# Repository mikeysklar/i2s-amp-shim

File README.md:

# i2s-amp-shim

A direct-connect shim PCB that mates the Adafruit I2S 3W Class D amp breakout (MAX98357A, **#3006**) to a Feather. No breadboard or jumper wires needed.

## About

A passive shim with no components: two right-angle SMD sockets and five traces. The Feather plugs into one edge. The amp plugs into the other edge, standing vertical with its parts facing away from the Feather. Both sockets overhang the board (75% on the Feather side, 61% on the amp side), which keeps the shim to 17.5 × 24.9 mm.

Single copper layer, made for a home build: the outline is milled and the copper is ablated with a fiber laser, then coated in solder mask with the pads opened. Design files are in [`kicad/`](kicad/). The board comes entirely from `kicad/build_pcb.py`.

## Pinout

| Feather | Amp (#3006) | Notes |
|---------|-------------|-------|
| 3V      | Vin         | |
| GND     | GND         | |
| A0      | BCLK        | |
| A1      | LRC         | must be the pin after BCLK for RP2xxx PIO I2S |
| A2      | DIN         | |
| —       | SD          | open: amp outputs (L+R)/2 mono |
| —       | GAIN        | open: 9 dB |

### CircuitPython usage

```python
import audiobusio, board
i2s = audiobusio.I2SOut(bit_clock=board.A0, word_select=board.A1, data=board.A2)
```

## Board notes

- **No crossings.** A0→BCLK and A1→LRC are straight across. A2→DIN runs under the south end of the amp socket and comes into pin 5 from behind.
- **Traces:** 1.0 mm, the full width of the socket pads, with at least 0.6 mm between traces.
- **GND** is a routed trace. The rest of the board is unconnected copper fill with a 0.5 mm gap around every trace and pad, so the laser has less to remove. The fill stays 0.5 mm back from the outline.
- **Front silk:** a label sits past each end of each socket's pin row, where the soldered socket doesn't cover it: 3V and A2 on the Feather side, VIN and LRC on the amp side.
- **Back silk** (burned with the laser): the board name, an A0/A1/A2 → BCLK/LRC/DIN table, and the date.
- **3D view:** the sockets use flat-SMT models made by `kicad/make_3d.py` (FreeCAD) from KiCad's right-angle socket. A Feather RP2350 and the #3006 amp are shown plugged in, using Adafruit's models from [Adafruit_CAD_Parts](https://github.com/adafruit/Adafruit_CAD_Parts). They're board-only, render-only footprints (VIS1, VIS2) with no copper, kept out of the schematic and BOM, and written by `kicad/gen_render_fps.py`.
- **Etch art:** `kicad/etch/etch-FCu-MIRRORED-1to1.pdf` (print at 100%) and `etch-FCu-reference.pdf`.

## Photos

### Laser-ablated copper

### Solder mask with the pads opened

### Assembled, next to its paste stencil

## Layout

## License

[MIT](LICENSE)

The KiCad-derived 3D models in `kicad/3dmodels/` are CC-BY-SA 4.0. The Adafruit board models are MIT, from Adafruit_CAD_Parts.

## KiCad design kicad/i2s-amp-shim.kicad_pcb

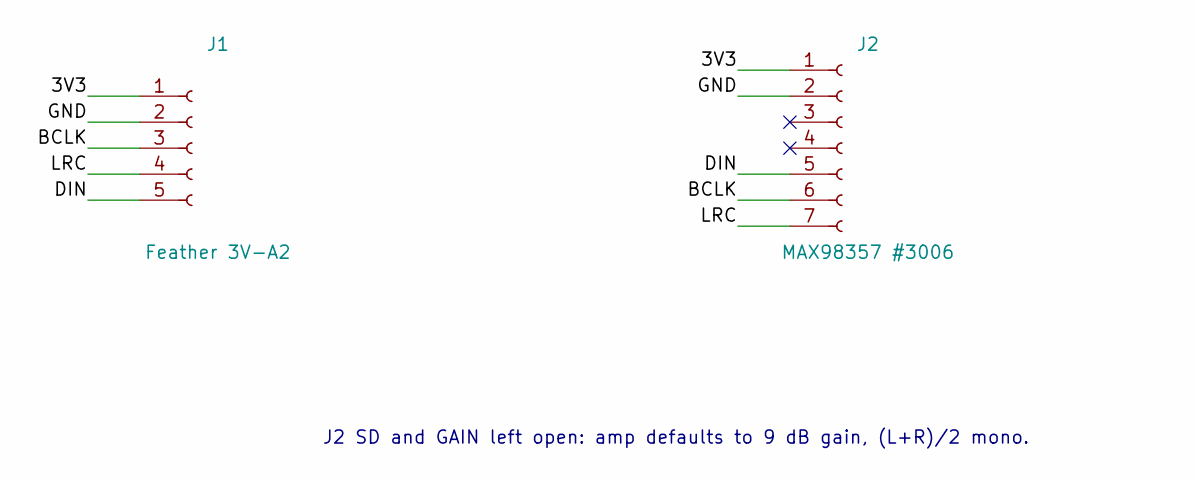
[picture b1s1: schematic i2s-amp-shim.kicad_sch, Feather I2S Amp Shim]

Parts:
J1: Feather 3V-A2; Feather_RtAngle_Socket_SMD_1x05
J2: MAX98357 #3006; Amp_RtAngle_Socket_SMD_1x07

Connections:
/3V3: J1.1, J2.1
/BCLK: J1.3, J2.6
/DIN: J1.5, J2.5
/GND: J1.2, J2.2
/LRC: J1.4, J2.7

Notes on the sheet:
J2 SD and GAIN left open: amp defaults to 9 dB gain, (L+R)/2 mono.

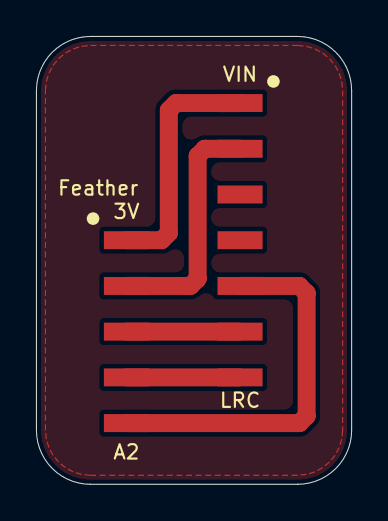
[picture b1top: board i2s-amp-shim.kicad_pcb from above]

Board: 2 copper layers, 17.5 x 24.9 mm, 4 parts (0 on the bottom side), 5 nets.

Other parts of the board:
VIS1: Render_Feather_RP2350_on_J1
VIS2: Render_MAX98357_on_J2
